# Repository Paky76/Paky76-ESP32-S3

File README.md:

# Paky76 Mini A5

Dispositivo portatile con due tasti laterali e un volto animato su **OLED SH1107G-02 da 1,5″, 128 × 128, I²C a 4 pin**. La A5 usa la **PCB principale A4** e il **frontale A1** già ordinati nella configurazione A4.1. Firmware, cablaggio, scocca e figure sono riferiti all'OLED quadrato.

## Documentazione

| Documento | Contenuto |
| --- | --- |
| [Manuale illustrato PDF](Documentazione/Paky76-Mini-A5-Manuale-Assemblaggio.pdf) | Stampa, montaggio, orientamento e collaudo |
| [Schema elettrico A3 · pagina unica](Documentazione/Paky76-Mini-A5-Schema-Elettrico.pdf) | Simboli elettrici, alimentazione, pull-up, pulsanti e OLED |
| [Tavola di cablaggio A3](Documentazione/Paky76-Mini-A5-Schema-Cablaggio-Completo.pdf) | Cablaggio tra i moduli con pin e segnali numerati |
| [Schemi di collegamento PDF](Documentazione/Paky76-Mini-A5-Schemi-Collegamento.pdf) | PCB, OLED, interruttore e batteria |
| [Datasheet PDF](Documentazione/Paky76-Mini-A5-Datasheet.pdf) | Specifiche e tavole quotate |
| [Figure e quote](Documentazione/Figure/) | Esploso, guscio, cornice, finestra, fori OLED e profilo |
| [Guida operativa](LEGGIMI.md) | Stampa, fissaggi, cablaggio, firmware e prove |

## Hardware e distinta per un dispositivo

| Qtà | Parte | Specifica |
| ---: | --- | --- |
| 1 | [Principale A4](Principale/) | 32 × 39 mm; USB-C, ingresso LiPo e pull-up I²C |
| 1 | [Frontale A1](Frontale/) | 43 × 42 mm; due tasti laterali e uscita OLED |
| 1 | U1 | Seeed XIAO ESP32-S3 113991114, C20467913 |
| 2 | J1 | JST SH 6 poli BM06B-SRSS-TB, C160392 |
| 1 | J2 frontale | JST SH 4 poli BM04B-SRSS-TB, C160390 |
| 2 | R1/R2 | 4,7 kΩ SMD 0603, C99782 |
| 2 | SW1/SW2 | Panasonic EVQP7A01P, C79167 |
| 1 | S1 | Nidec MFS201N-Z, a slitta sul fianco |
| 1 | OLED | SH1107G-02; PCB 34 × 47 mm; spessore massimo dichiarato 11,3 mm; area visibile 28,86 × 28,86 mm |
| 1 | Batteria | LiPo protetta 1S, 3,7 V nominali, 4,2 V a fine carica. Riferimento 350 mAh |
| 1 ciascuno | Cavetti | JST SH 6 vie pin per pin, JST SH 4 vie con fili lato OLED, contropresa batteria, cavo USB-C dati |
| Secondo montaggio | Fissaggi e accessori | Viti M2 da scegliere a secco, guaina isolante, ritenzione morbida cella, antenna XIAO se assente |

I [file JLCPCB](JLCPCB/) contengono Gerber, BOM e CPL per ciascuna scheda. Per PCB nudi, U1 richiede anche la saldatura dei due pad batteria sotto il modulo. Per PCBA, controllare in anteprima orientamento, componenti e montaggio.

## Cablaggio e alimentazione

**J1 principale ↔ J1 frontale**, pin per pin. 1 GND, 2 3V3, 3 SDA/GPIO5, 4 SCL/GPIO6, 5 SW1/GPIO2, 6 SW2/GPIO1. I pulsanti sono attivi bassi.

| J2 frontale | Funzione | Pin OLED secondo il disegno |
| ---: | --- | ---: |
| 1 | GND | 2 |
| 2 | 3V3 verso VCC | 1 |
| 3 | SDA | 4 |
| 4 | SCL | 3 |

Il testo commerciale e il disegno OLED riportano numerazioni di alimentazione diverse. **Seguire le serigrafie sul modulo ricevuto e collegare per segnale.** Passo JST SH 1,0 mm; lato OLED 2,54 mm. Vedere il [pinout](Cablaggio/Pinout-OLED-SH1107.md).

Il **J2 della principale** porta il positivo LiPo sul pin 1 VBAT attraverso S1 e il negativo diretto sul pin 2 GND. La prima accensione si fa via USB con batteria scollegata. Per ricaricare, portare S1 su ON. Per togliere tutta l'alimentazione, mettere S1 su OFF e scollegare USB-C.

## Scocca, montaggio e firmware

1. La scocca misura **49 × 54 × 41,6 mm**, escluse le sporgenze, e **61,5 mm** in lunghezza con occhiello. Finestra **30,4 × 30,4 mm**, centrata 3 mm verso USB-C nel CAD. Interasse nominale di fissaggio OLED **29 × 42 mm**, da confrontare con il campione.
2. In Cura importare gli [STL A5](Meccanica/) al 100%. Stampare un guscio, una cornice e due copritasti. Confrontare la dima OLED con il modulo reale prima della stampa definitiva. Il sorgente OpenSCAD è nella stessa cartella.
3. Installare S1 e la principale con USB-C opposta all'occhiello. Verificare a secco ripiano, batteria, frontale, copritasti e OLED. Montare secondo le figure, con il vetro verso la finestra e J2 del frontale verso USB-C.
4. Installare il core esp32 di Espressif e U8g2 in Arduino IDE, selezionare XIAO_ESP32S3 e usare lo [sketch A5](Firmware/Paky76MiniSH1107/Paky76MiniSH1107.ino). Il firmware cerca 0x3C e 0x3D a 100 kHz, anima il volto e risveglia il display con uno dei tasti dopo lo spegnimento per inattività. Monitor seriale a 115200 baud.
5. Verificare display, tasti e continuità prima di collegare la LiPo. Sul campione controllare passaggio dei cavi, assenza di compressione sulla cella, ricarica e temperatura con la scocca chiusa.

## Stato delle prove

I [rapporti](Verifiche/) registrano l'identità byte per byte delle PCB e dei file JLCPCB con la A4.1, il controllo delle mesh STL e la simulazione host della logica firmware. **Compilazione per la XIAO e collaudo fisico restano da eseguire.** Le quote di montaggio OLED e la corsa dei copritasti vanno verificate sul primo campione.

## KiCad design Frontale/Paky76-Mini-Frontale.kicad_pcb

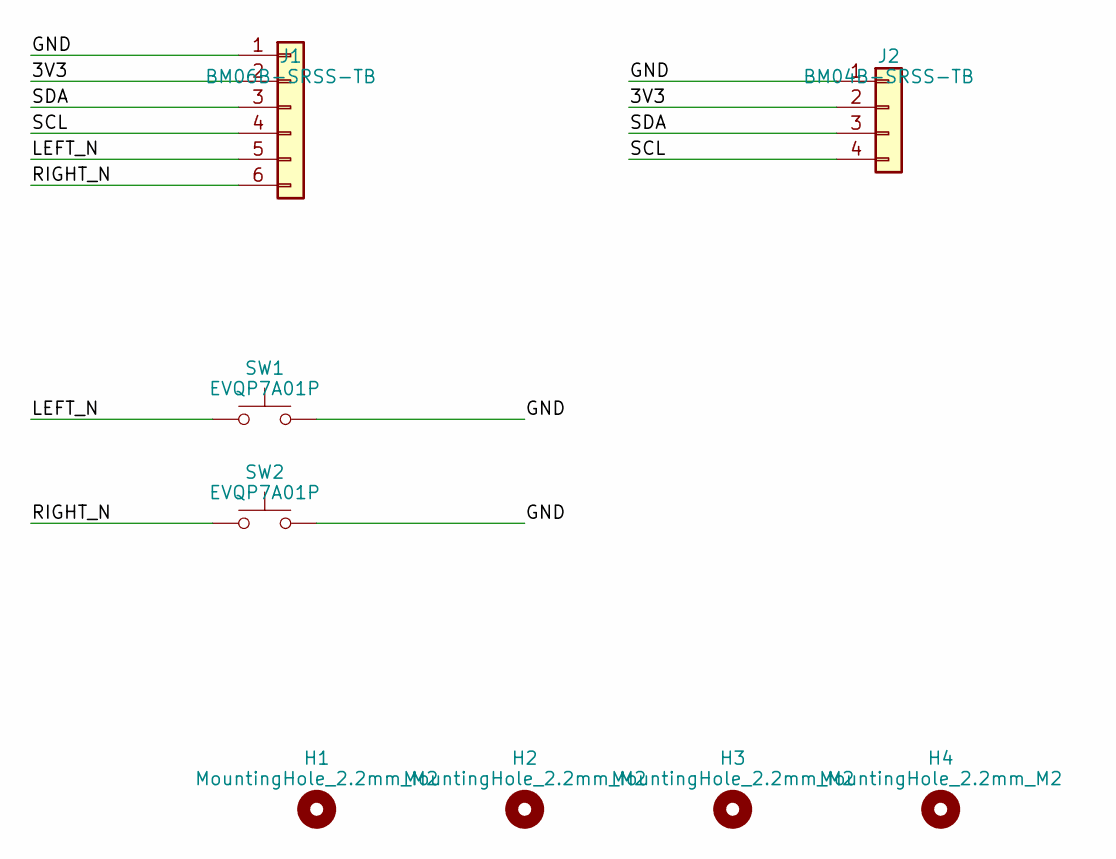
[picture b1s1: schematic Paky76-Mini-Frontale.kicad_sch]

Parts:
H1, H2, H3, H4: MountingHole_2.2mm_M2
J1: BM06B-SRSS-TB; JST_SH_BM06B-SRSS-TB_1x06-1MP_P1.00mm_Vertical
J2: BM04B-SRSS-TB; JST_SH_BM04B-SRSS-TB_1x04-1MP_P1.00mm_Vertical
SW1, SW2: EVQP7A01P; SW_SPST_EVQP7A

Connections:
/3V3: J1.2, J2.2
/GND: J1.1, J2.1, SW1.2, SW2.2
/LEFT_N: J1.5, SW1.1
/RIGHT_N: J1.6, SW2.1
/SCL: J1.4, J2.4
/SDA: J1.3, J2.3

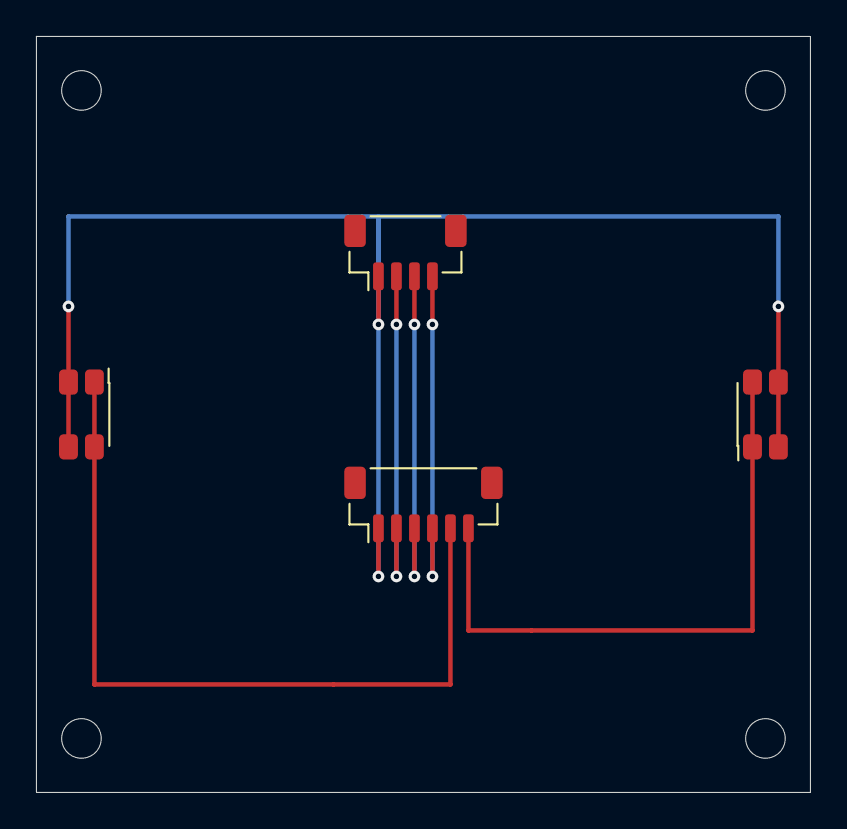
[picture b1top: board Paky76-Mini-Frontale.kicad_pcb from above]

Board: 2 copper layers, 43.0 x 42.0 mm, 8 parts (0 on the bottom side), 6 nets.

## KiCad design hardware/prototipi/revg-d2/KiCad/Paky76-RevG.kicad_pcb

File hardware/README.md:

# Hardware design workspace — Rev.A

Target: ESP32-S3-WROOM-1-based controller with external Waveshare 1.3inch LCD Module (ST7789, 240x240).

**No KiCad schematic or PCB has yet passed validation.** Do not send this directory to a board manufacturer.

## Provisional net allocation
| Net | ESP32-S3 GPIO | Peripheral |
|---|---:|---|
| LCD_MOSI | 11 | ST7789 DIN |
| LCD_SCLK | 12 | ST7789 CLK |
| LCD_CS | 10 | ST7789 CS |
| LCD_DC | 9 | ST7789 DC |
| LCD_RST | 8 | ST7789 RST |
| LCD_BL | 7 | ST7789 BL (driver TBD) |
| USB_DN | 19 | USB D- |
| USB_DP | 20 | USB D+ |

Verify the exact Waveshare module pin sequence and mating connector orientation before routing. GPIO7 must not be connected directly to a high-current backlight load without checking the module's BL interface.

## Design blocks to capture in KiCad
1. U1 ESP32-S3-WROOM-1, validated footprint and antenna keepout.
2. J1 USB-C receptacle, USB2.0 D+/D-, CC resistors and ESD.
3. U2 3.3 V regulator sized for ESP32-S3 radio bursts and display.
4. Boot/reset circuitry, EN pull-up and programming access.
5. LCD 8-pin PH2.0 mating connector, pin-1 orientation checked.
6. Power decoupling, test points, mounting and mechanical outline.

Manufacturing deliverables are gated on actual KiCad ERC/DRC and independent review.

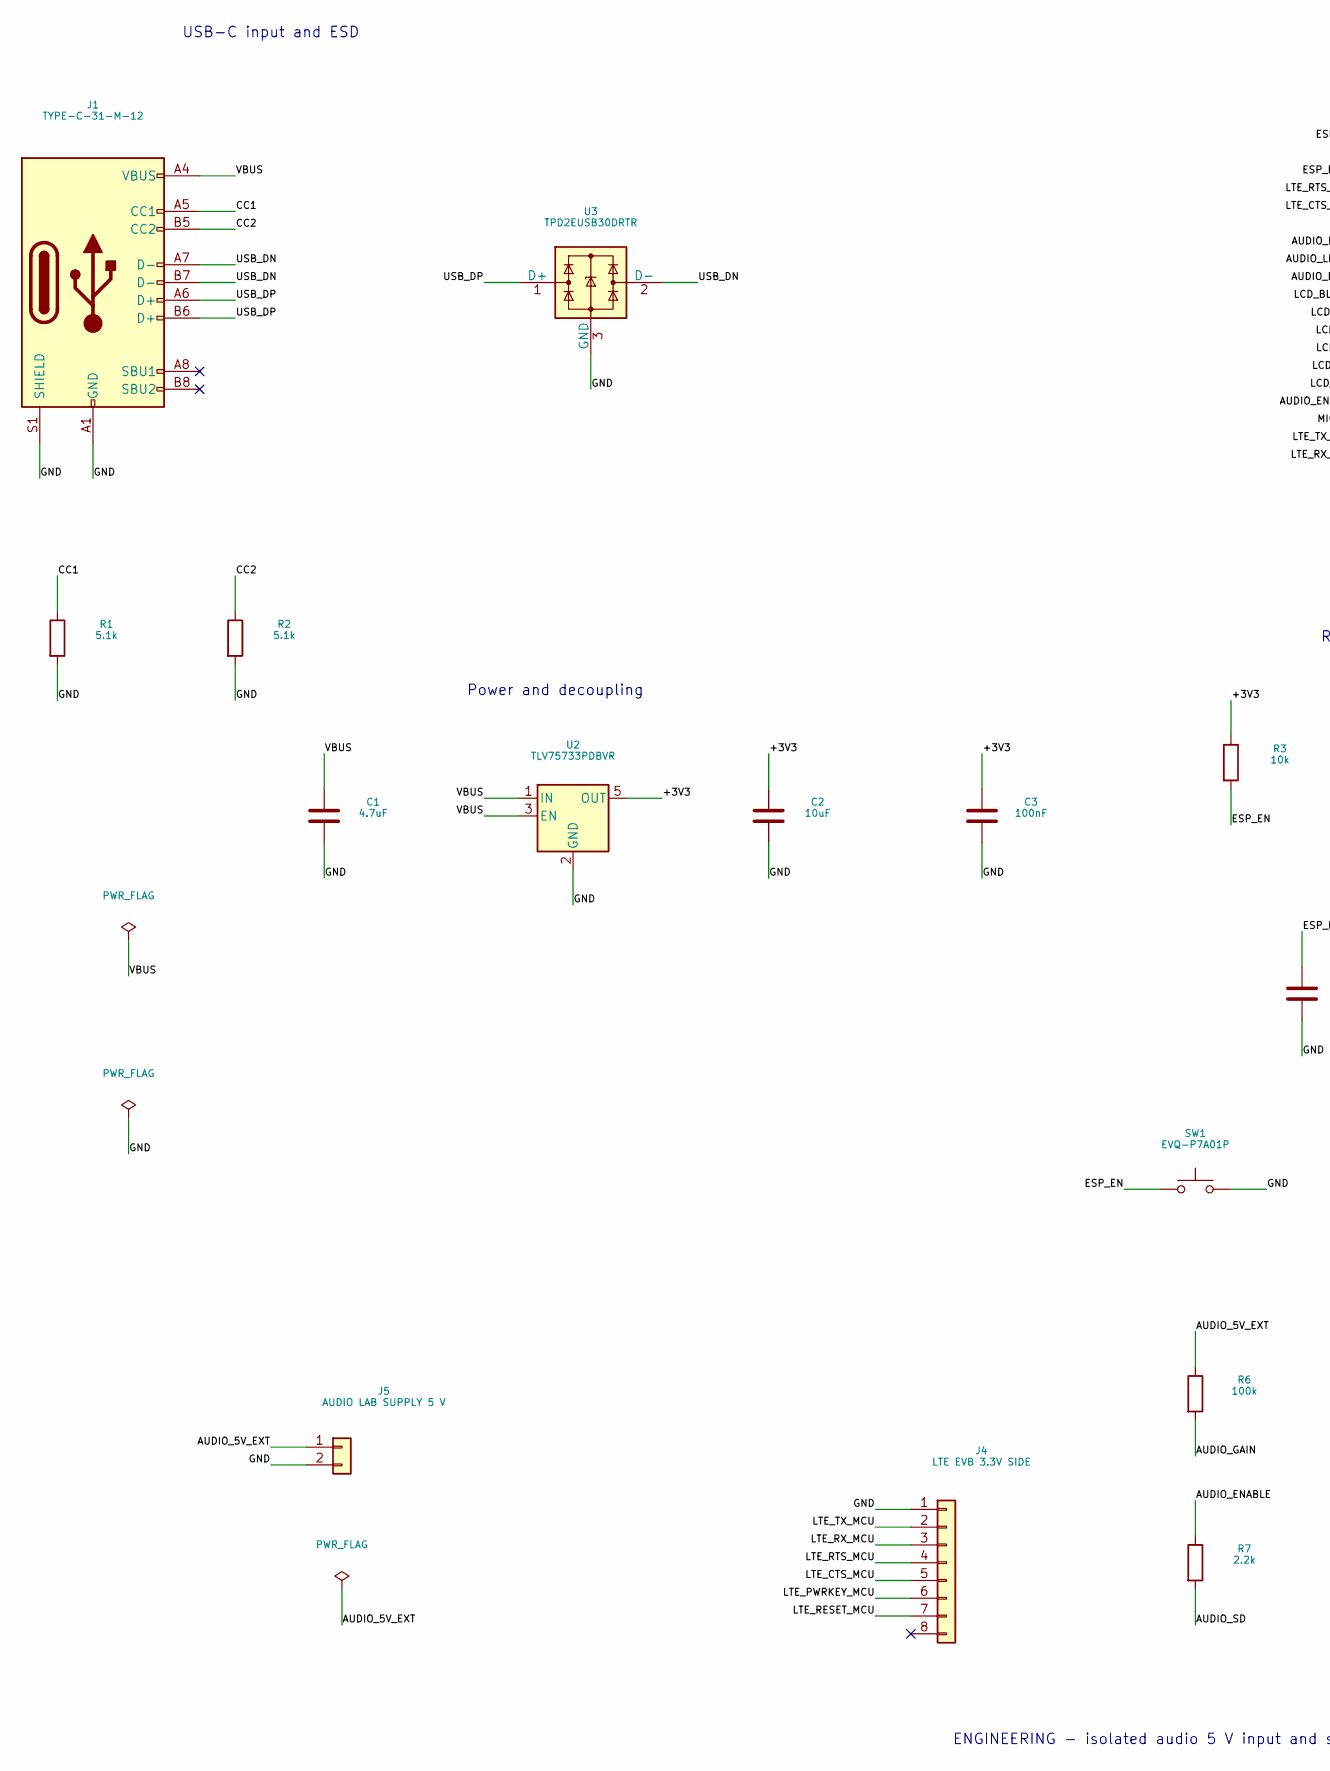
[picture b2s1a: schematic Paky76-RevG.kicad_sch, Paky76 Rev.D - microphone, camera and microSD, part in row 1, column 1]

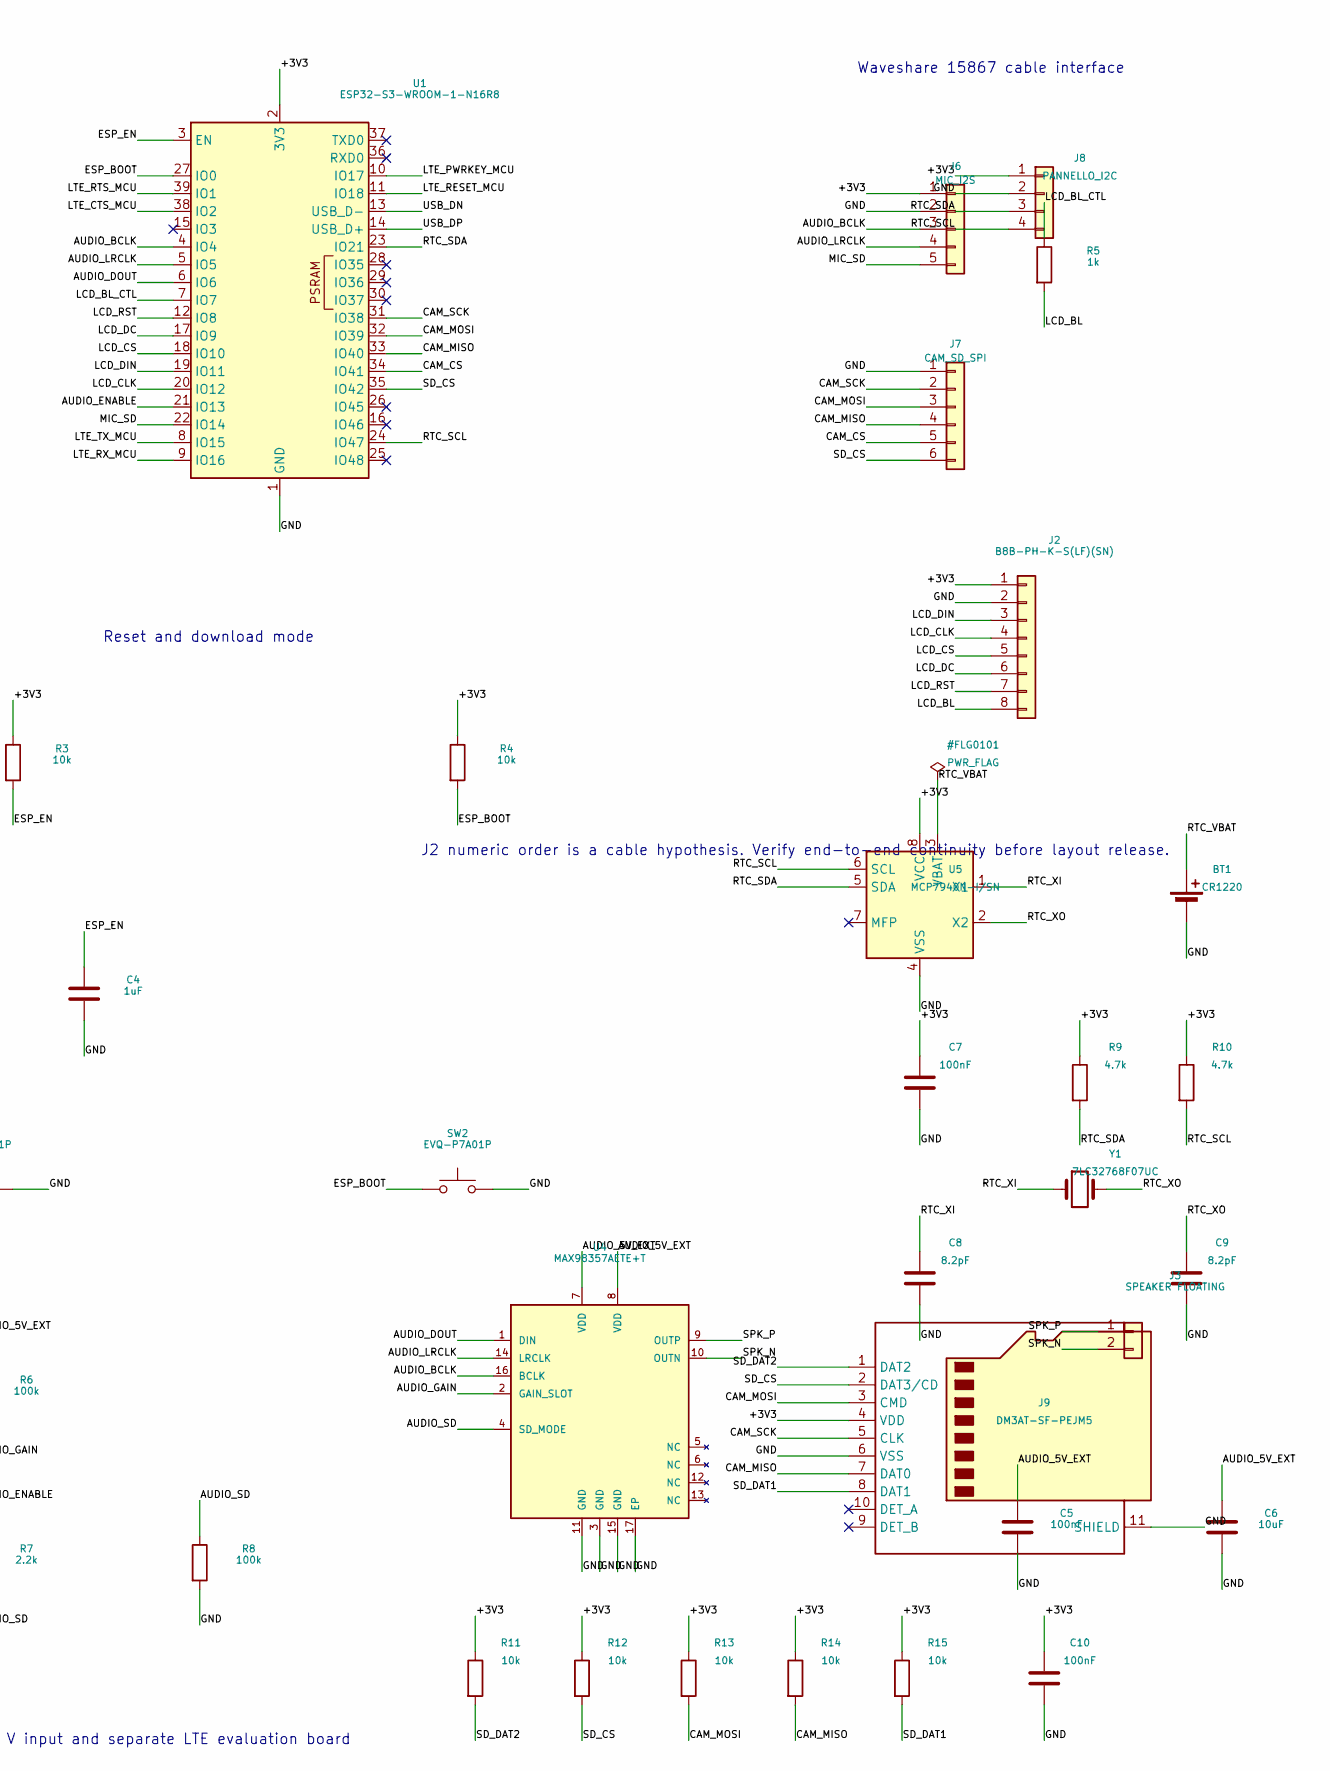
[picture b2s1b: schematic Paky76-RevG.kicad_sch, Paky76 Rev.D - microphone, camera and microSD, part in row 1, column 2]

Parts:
BT1: CR1220; BatteryHolder_Keystone_500
C1: 4.7uF; C_0805_2012Metric
C2, C6: 10uF; C_0805_2012Metric
C3, C5, C7, C10: 100nF; C_0603_1608Metric
C4: 1uF; C_0603_1608Metric
C8, C9: 8.2pF; C_0603_1608Metric
J1: TYPE-C-31-M-12; USB_C_HRO_TYPE-C-31-M-12_Edge
J2: B8B-PH-K-S(LF)(SN); JST_PH_B8B-PH-K_1x08_P2.00mm_Vertical
J3: SPEAKER FLOATING; JST_PH_B2B-PH-K_1x02_P2.00mm_Vertical
J4: LTE EVB 3.3V SIDE; PinHeader_1x08_P2.54mm_Vertical
J5: AUDIO LAB SUPPLY 5 V; JST_PH_B2B-PH-K_1x02_P2.00mm_Vertical
J6: MIC_I2S; JST_PH_B5B-PH-K_1x05_P2.00mm_Vertical
J7: CAM_SD_SPI; JST_PH_B6B-PH-K_1x06_P2.00mm_Vertical
J8: PANNELLO_I2C; JST_SH_BM04B-SRSS-TB_1x04-1MP_P1.00mm_Vertical
J9: DM3AT-SF-PEJM5; microSD_HC_Hirose_DM3AT-SF-PEJM5
R1, R2: 5.1k; R_0603_1608Metric
R3, R4, R11, R12, R13, R14, R15: 10k; R_0603_1608Metric
R5: 1k; R_0603_1608Metric
R6, R8: 100k; R_0603_1608Metric
R7: 2.2k; R_0603_1608Metric
R9, R10: 4.7k; R_0603_1608Metric
SW1, SW2: EVQ-P7A01P; SW_SPST_EVQP7A
U1: ESP32-S3-WROOM-1-N16R8; ESP32-S3-WROOM-1_4L_Overhang
U2: TLV75733PDBVR; SOT-23-5
U3: TPD2EUSB30DRTR; Texas_DRT-3
U4: MAX98357AETE+T; MAX98357A_T1633_90-0031
U5: MCP7940N-I/SN; SOIC-8_3.9x4.9mm_P1.27mm
Y1: 7LC32768F07UC; Crystal_SMD_3215-2Pin_3.2x1.5mm

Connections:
/+3V3: C2.1, C3.1, C7.1, C10.1, J2.1, J6.1, J8.1, J9.4 (VDD), R3.1, R4.1, R9.1, R10.1, R11.1, R12.1, R13.1, R14.1, R15.1, U1.2 (3V3), U2.5 (OUT), U5.8 (VCC)
/AUDIO_5V_EXT: C5.1, C6.1, J5.1, R6.1, U4.7 (VDD), U4.8 (VDD)
/AUDIO_BCLK: J6.3, U1.4 (IO4), U4.16 (BCLK)
/AUDIO_DOUT: U1.6 (IO6), U4.1 (DIN)
/AUDIO_ENABLE: R7.1, U1.21 (IO13)
/AUDIO_GAIN: R6.2, U4.2 (GAIN_SLOT)
/AUDIO_LRCLK: J6.4, U1.5 (IO5), U4.14 (LRCLK)
/AUDIO_SD: R7.2, R8.1, U4.4 (SD_MODE)
/CAM_CS: J7.5, U1.34 (IO41)
/CAM_MISO: J7.4, J9.7 (DAT0), R14.2, U1.33 (IO40)
/CAM_MOSI: J7.3, J9.3 (CMD), R13.2, U1.32 (IO39)
/CAM_SCK: J7.2, J9.5 (CLK), U1.31 (IO38)
/CC1: J1.A5 (CC1), R1.1
/CC2: J1.B5 (CC2), R2.1
/ESP_BOOT: R4.2, SW2.1, U1.27 (IO0)
/ESP_EN: C4.1, R3.2, SW1.1, U1.3 (EN)
/GND: BT1.2 (-), C1.2, C2.2, C3.2, C4.2, C5.2, C6.2, C7.2, C8.2, C9.2, C10.2, J1.A1 (GND), J1.A12 (GND), J1.B1 (GND), J1.B12 (GND), J1.S1 (SHIELD), J2.2, J4.1, J5.2, J6.2, J7.1, J8.2, J9.6 (VSS), J9.11 (SHIELD), R1.2, R2.2, R8.2, SW1.2, SW2.2, U1.1 (GND), U1.40 (GND), U1.41 (GND), U2.2 (GND), U3.3 (GND), U4.3 (GND), U4.11 (GND), U4.15 (GND), U4.17 (EP), U5.4 (VSS)
/LCD_BL: J2.8, R5.2
/LCD_BL_CTL: R5.1, U1.7 (IO7)
/LCD_CLK: J2.4, U1.20 (IO12)
/LCD_CS: J2.5, U1.18 (IO10)
/LCD_DC: J2.6, U1.17 (IO9)
/LCD_DIN: J2.3, U1.19 (IO11)
/LCD_RST: J2.7, U1.12 (IO8)
/LTE_CTS_MCU: J4.5, U1.38 (IO2)
/LTE_PWRKEY_MCU: J4.6, U1.10 (IO17)
/LTE_RESET_MCU: J4.7, U1.11 (IO18)
/LTE_RTS_MCU: J4.4, U1.39 (IO1)
/LTE_RX_MCU: J4.3, U1.9 (IO16)
/LTE_TX_MCU: J4.2, U1.8 (IO15)
/MIC_SD: J6.5, U1.22 (IO14)
/RTC_SCL: J8.4, R10.2, U1.24 (IO47), U5.6 (SCL)
/RTC_SDA: J8.3, R9.2, U1.23 (IO21), U5.5 (SDA)
/RTC_VBAT: BT1.1 (+), U5.3 (VBAT)
/RTC_XI: C8.1, U5.1 (X1), Y1.1
/RTC_XO: C9.1, U5.2 (X2), Y1.2
/SD_CS: J7.6, J9.2 (DAT3/CD), R12.2, U1.35 (IO42)
/SD_DAT1: J9.8 (DAT1), R15.2
/SD_DAT2: J9.1 (DAT2), R11.2
/SPK_N: J3.2, U4.10 (OUTN)
/SPK_P: J3.1, U4.9 (OUTP)
/USB_DN: J1.A7 (D-), J1.B7 (D-), U1.13 (USB_D-), U3.2 (D-)
/USB_DP: J1.A6 (D+), J1.B6 (D+), U1.14 (USB_D+), U3.1 (D+)
/VBUS: C1.1, J1.A4 (VBUS), J1.A9 (VBUS), J1.B4 (VBUS), J1.B9 (VBUS), U2.1 (IN), U2.3 (EN)

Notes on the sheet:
USB-C input and ESD
Power and decoupling
Reset and download mode
Waveshare 15867 cable interface
J2 numeric order is a cable hypothesis. Verify end-to-end continuity before layout release.
ENGINEERING - isolated audio 5 V input and separate LTE evaluation board

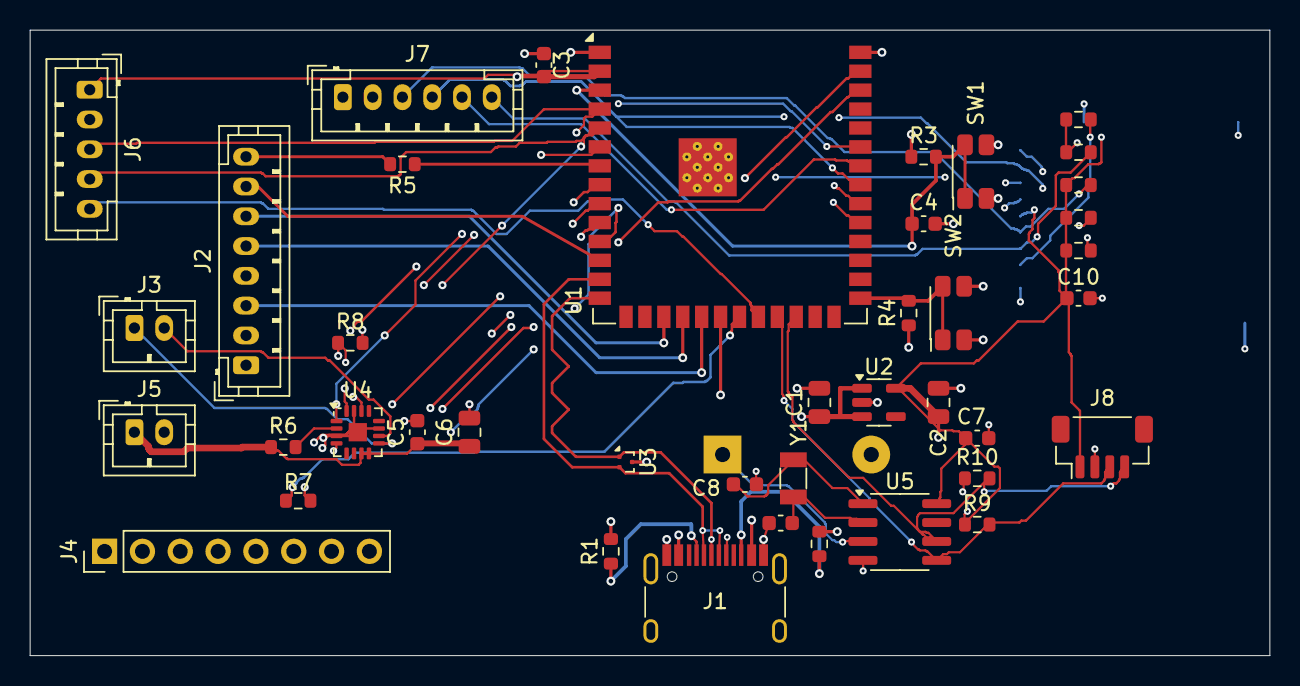
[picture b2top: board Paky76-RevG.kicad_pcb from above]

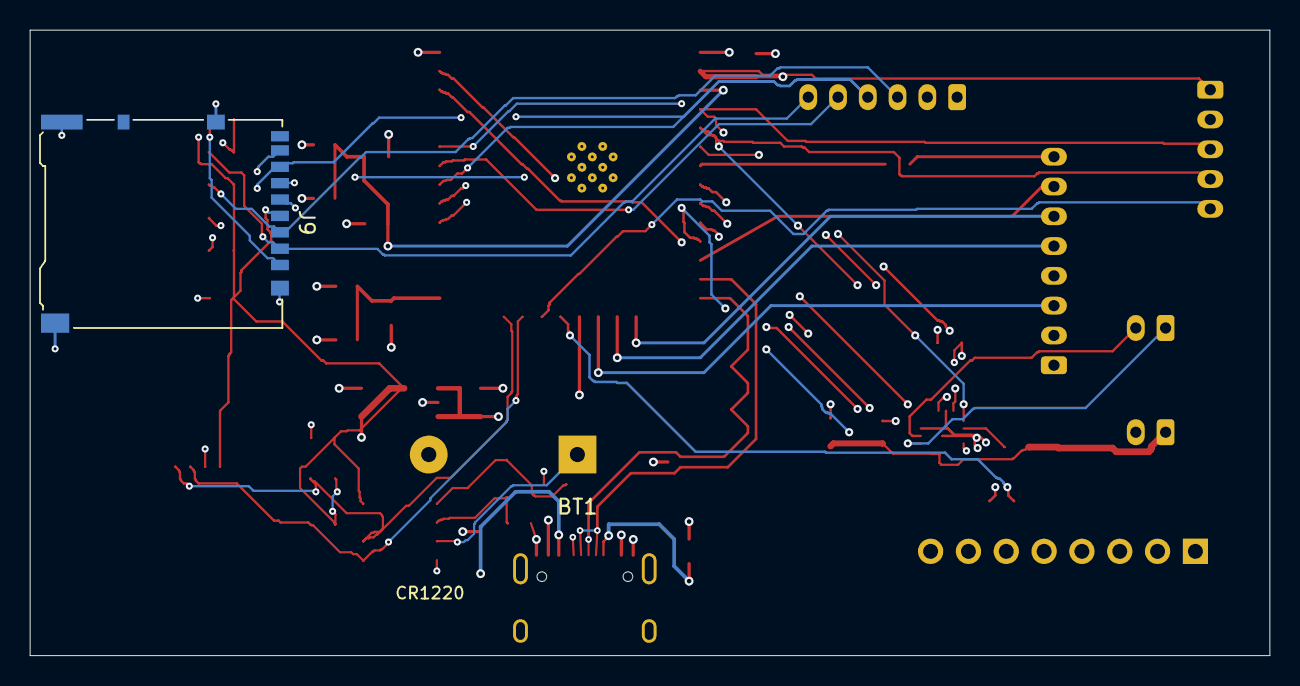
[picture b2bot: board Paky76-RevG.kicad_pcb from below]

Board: 4 copper layers, 83.2 x 42.0 mm, 43 parts (2 on the bottom side), 44 nets.

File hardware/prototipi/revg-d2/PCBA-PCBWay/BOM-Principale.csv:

Comment,Designator,Footprint,Manufacturer Part Number,LCSC Part #
4.7uF,C1,C_0805_2012Metric,GRM21BR71C475KA73L,C86040
10uF,"C2,C6",C_0805_2012Metric,GRM21BR71A106KE51L,C86038
100nF,"C3,C5,C7,C10",C_0603_1608Metric,GRM188R71C104KA01D,C45000
1uF,C4,C_0603_1608Metric,GRT188R71C105KE13D,C6627646
TYPE-C-31-M-12,J1,USB_C_HRO_TYPE-C-31-M-12_Edge,TYPE-C-31-M-12,C165948
B8B-PH-K-S(LF)(SN),J2,JST_PH_B8B-PH-K_1x08_P2.00mm_Vertical,B8B-PH-K-S(LF)(SN),C157974
B2B-PH-K-S(LF)(SN),"J3,J5",JST_PH_B2B-PH-K_1x02_P2.00mm_Vertical,B2B-PH-K-S(LF)(SN),C131337
LTE EVB 3.3V SIDE,J4,PinHeader_1x08_P2.54mm_Vertical,TSW-108-07-G-S,C3335496
5.1k,"R1,R2",R_0603_1608Metric,RC0603FR-075K1L,C105580
10k,"R3,R4,R11,R12,R13,R14,R15",R_0603_1608Metric,RC0603FR-0710KL,C98220
1k,R5,R_0603_1608Metric,RC0603FR-071KL,C22548
100k,"R6,R8",R_0603_1608Metric,RC0603FR-07100KL,C14675
2.2k,R7,R_0603_1608Metric,RC0603FR-072K2L,C114662
EVQ-P7A01P,"SW1,SW2",SW_SPST_EVQP7A,EVQP7A01P,C79167
ESP32-S3-WROOM-1-N16R8,U1,ESP32-S3-WROOM-1_4L_Overhang,ESP32-S3-WROOM-1-N16R8,C2913202
TLV75733PDBVR,U2,SOT-23-5,TLV75733PDBVR,C485517
TPD2EUSB30DRTR,U3,Texas_DRT-3,TPD2EUSB30DRTR,C97502
MAX98357AETE+T,U4,MAX98357A_T1633_90-0031,MAX98357AETE+T,C910544
B5B-PH-K-S(LF)(SN),J6,JST_PH_B5B-PH-K_1x05_P2.00mm_Vertical,B5B-PH-K-S(LF)(SN),C157993
B6B-PH-K-S(LF)(SN),J7,JST_PH_B6B-PH-K_1x06_P2.00mm_Vertical,B6B-PH-K-S(LF)(SN),C131342
4.7k,"R9,R10",R_0603_1608Metric,RC0603FR-074K7L,C99782
MCP7940N-I/SN,U5,SOIC-8_3.9x4.9mm_P1.27mm,MCP7940N-I/SN,C51106
CR1220 holder,BT1,BatteryHolder_Keystone_500,500,C238121
32.768kHz 7pF,Y1,Crystal_SMD_3215-2Pin_3.2x1.5mm,7LC32768F07UC,C252399
8.2pF C0G,"C8,C9",C_0603_1608Metric,TCC0603COG8R2C500CT,C376804
BM04B-SRSS-TB,J8,JST_SH_BM04B-SRSS-TB_1x04-1MP_P1.00mm_Vertical,BM04B-SRSS-TB(LF)(SN),C160390
Hirose microSD,J9,microSD_HC_Hirose_DM3AT-SF-PEJM5,DM3AT-SF-PEJM5,C114218

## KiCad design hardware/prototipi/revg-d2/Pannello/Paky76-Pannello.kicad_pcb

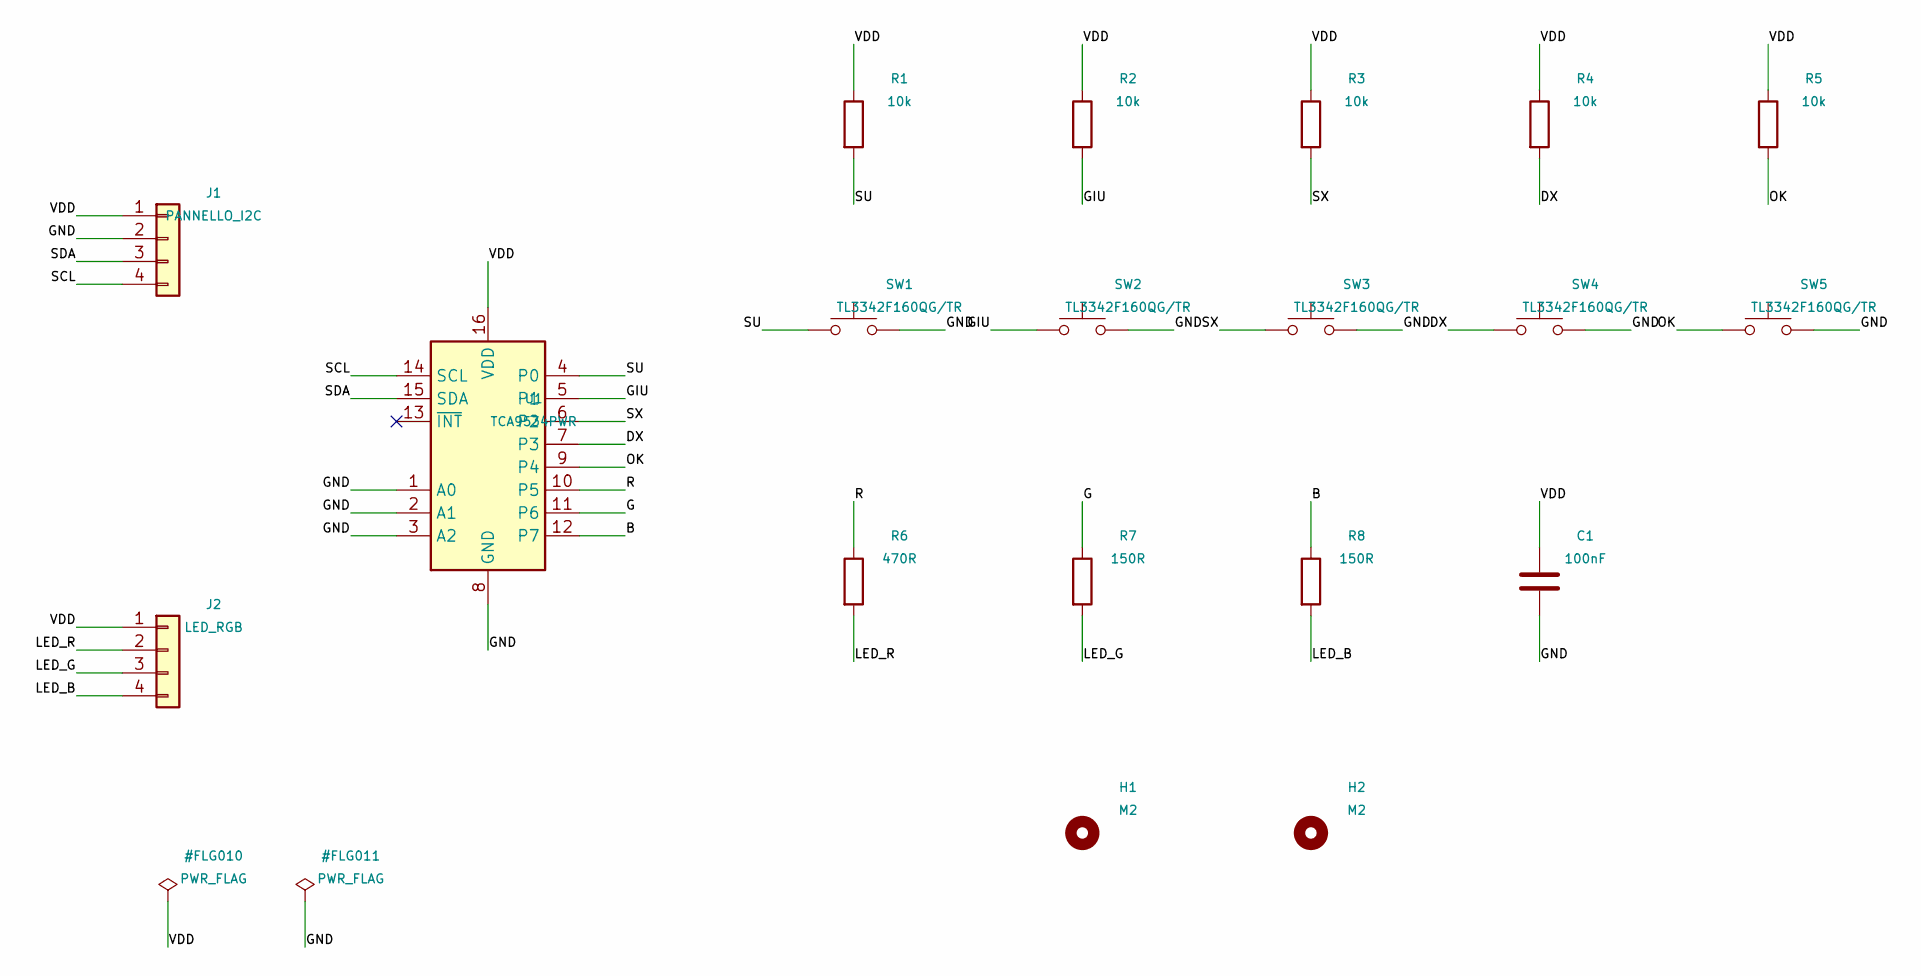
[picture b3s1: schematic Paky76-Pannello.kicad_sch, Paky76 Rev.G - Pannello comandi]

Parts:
C1: 100nF; C_0603_1608Metric
H1, H2: M2; MountingHole_2.2mm_M2
J1: PANNELLO_I2C; JST_SH_BM04B-SRSS-TB_1x04-1MP_P1.00mm_Vertical
J2: LED_RGB; JST_SH_BM04B-SRSS-TB_1x04-1MP_P1.00mm_Vertical
R1, R2, R3, R4, R5: 10k; R_0603_1608Metric
R6: 470R; R_0603_1608Metric
R7, R8: 150R; R_0603_1608Metric
SW1, SW2, SW3, SW4, SW5: TL3342F160QG/TR; SW_SPST_TL3342
U1: TCA9534PWR; TSSOP-16_4.4x5mm_P0.65mm

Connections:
/B: R8.1, U1.12 (P7)
/DX: R4.2, SW4.1, U1.7 (P3)
/G: R7.1, U1.11 (P6)
/GIU: R2.2, SW2.1, U1.5 (P1)
/GND: C1.2, J1.2, SW1.2, SW2.2, SW3.2, SW4.2, SW5.2, U1.1 (A0), U1.2 (A1), U1.3 (A2), U1.8 (GND)
/LED_B: J2.4, R8.2
/LED_G: J2.3, R7.2
/LED_R: J2.2, R6.2
/OK: R5.2, SW5.1, U1.9 (P4)
/R: R6.1, U1.10 (P5)
/SCL: J1.4, U1.14 (SCL)
/SDA: J1.3, U1.15 (SDA)
/SU: R1.2, SW1.1, U1.4 (P0)
/SX: R3.2, SW3.1, U1.6 (P2)
/VDD: C1.1, J1.1, J2.1, R1.1, R2.1, R3.1, R4.1, R5.1, U1.16 (VDD)

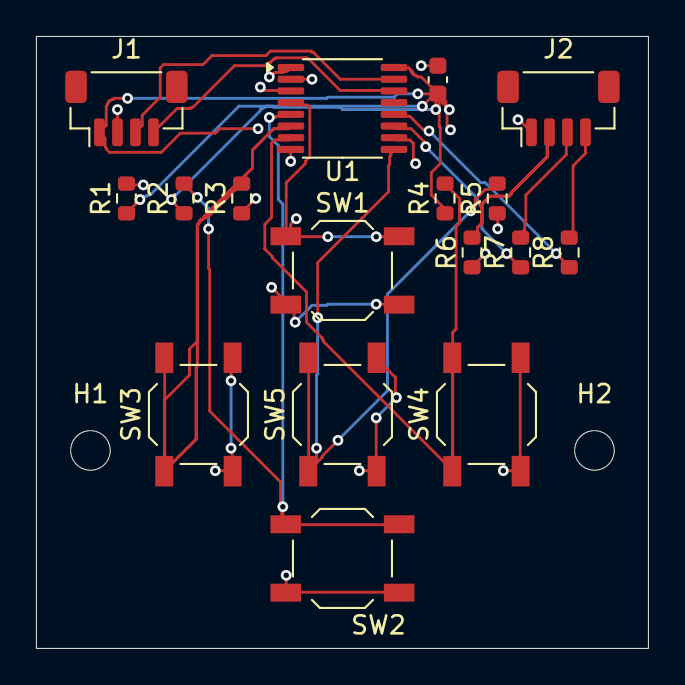
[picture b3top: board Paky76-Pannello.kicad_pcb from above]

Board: 4 copper layers, 34.0 x 34.0 mm, 19 parts (0 on the bottom side), 15 nets.

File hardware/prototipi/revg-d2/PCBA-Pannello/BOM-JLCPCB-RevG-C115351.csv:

Comment,Designator,Footprint,Manufacturer Part Number,LCSC Part #
100nF,C1,C_0603_1608Metric,GRM188R71C104KA01D,C45000
BM04B-SRSS-TB,"J1,J2",JST_SH_BM04B-SRSS-TB_1x04-1MP_P1.00mm_Vertical,BM04B-SRSS-TB(LF)(SN),C160390
TCA9534,U1,TSSOP-16_4.4x5mm_P0.65mm,TCA9534PWR,C783615
Five tactile switches,"SW1,SW2,SW3,SW4,SW5",SW_SPST_TL3342,SKQGABE010,C115351
10k,"R1,R2,R3,R4,R5",R_0603_1608Metric,RC0603FR-0710KL,C98220
470R,R6,R_0603_1608Metric,RC0603FR-07470RL,C114669
150R,"R7,R8",R_0603_1608Metric,RC0603FR-07150RL,C114608

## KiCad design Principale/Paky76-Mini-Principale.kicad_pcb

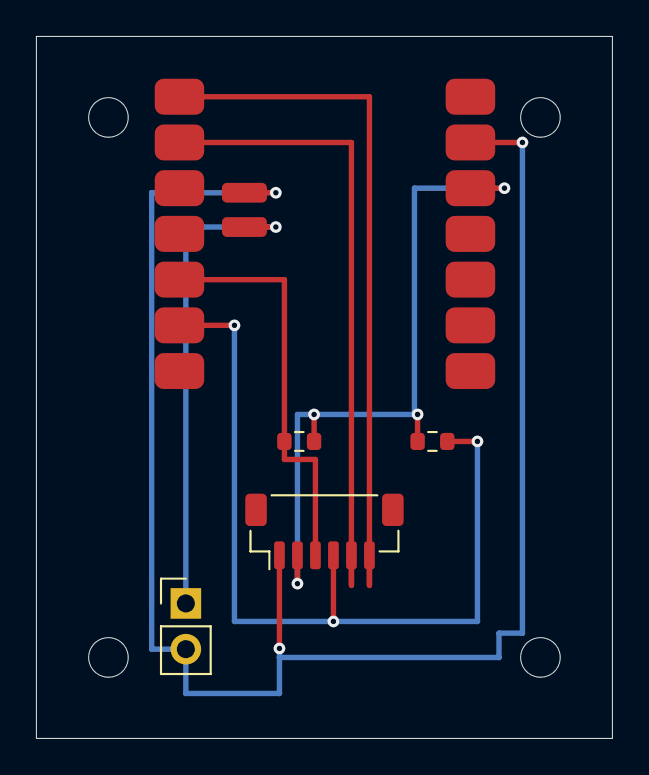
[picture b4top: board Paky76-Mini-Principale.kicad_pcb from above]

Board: 2 copper layers, 32.0 x 39.0 mm, 9 parts (0 on the bottom side), 7 nets.

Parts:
H1, H2, H3, H4: MountingHole_2.2mm_M2
J1: BM06B-SRSS-TB; JST_SH_BM06B-SRSS-TB_1x06-1MP_P1.00mm_Vertical
J2: BAT-SW; PinHeader_1x02_P2.54mm_Vertical
R1, R2: 4.7k; R_0603_1608Metric
U1: 113991114; XIAO-ESP32-S3-PCBA

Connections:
/3V3: J1.2, R1.2, R2.1, U1.12
/GND: J1.1, J2.2, U1.13, U1.16
/LEFT_N: J1.5, U1.2
/RIGHT_N: J1.6, U1.1
/SCL: J1.4, R2.2, U1.6
/SDA: J1.3, R1.1, U1.5
/VBAT: J2.1, U1.15

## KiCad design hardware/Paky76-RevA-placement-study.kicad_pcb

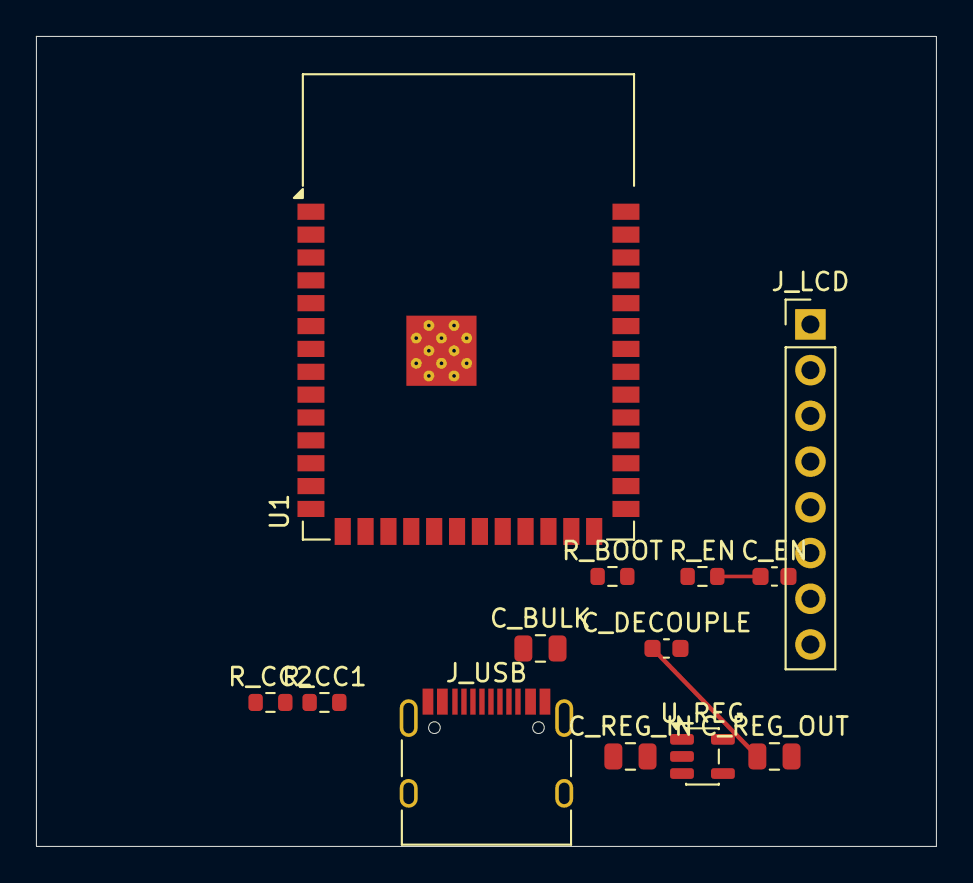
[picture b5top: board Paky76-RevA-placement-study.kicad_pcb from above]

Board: 2 copper layers, 50.0 x 45.0 mm, 13 parts (0 on the bottom side), 15 nets.

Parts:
C_BULK: 10uF_PLACEHOLDER; C_0805_2012Metric
C_DECOUPLE: 100nF_PLACEHOLDER; C_0603_1608Metric
C_EN: 1uF_CANDIDATE; C_0603_1608Metric
C_REG_IN: 10uF_CANDIDATE; C_0805_2012Metric
C_REG_OUT: 10uF_CANDIDATE; C_0805_2012Metric
J_LCD: DISPLAY_INTERFACE_STUDY_ONLY; PinHeader_1x08_P2.54mm_Vertical
J_USB: USB-C_FOOTPRINT_STUDY; USB_C_Receptacle_HRO_TYPE-C-31-M-12
R_BOOT: 10k_CANDIDATE; R_0603_1608Metric
R_CC1, R_CC2: 5.1k; R_0603_1608Metric
R_EN: 10k_CANDIDATE; R_0603_1608Metric
U1: ESP32-S3-WROOM-1-N8; ESP32-S3-WROOM-1
U_REG: AP2112K-3.3TRG1_CANDIDATE; SOT-23-5

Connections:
+3V3: C_DECOUPLE.1, C_REG_OUT.1, J_LCD.2, R_BOOT.1, R_EN.1, U1.2, U_REG.5
ESP_EN: C_EN.1, R_EN.2, U1.3
ESP_GPIO0_BOOT: R_BOOT.2, U1.27
GND: C_BULK.2, C_DECOUPLE.2, C_EN.2, C_REG_IN.2, C_REG_OUT.2, J_LCD.1, J_USB.A1, J_USB.A12, J_USB.B1, J_USB.B12, R_CC1.2, R_CC2.2, U1.1, U1.40, U1.41, U_REG.2
LCD_BL: J_LCD.8, U1.7
LCD_CS: J_LCD.7, U1.18
LCD_DC: J_LCD.6, U1.17
LCD_MOSI: J_LCD.4, U1.19
LCD_RST: J_LCD.5, U1.12
LCD_SCLK: J_LCD.3, U1.20
USB_CC1: J_USB.A5, R_CC1.1
USB_CC2: J_USB.B5, R_CC2.1
USB_DN: J_USB.A7, J_USB.B7, U1.13
USB_DP: J_USB.A6, J_USB.B6, U1.14
USB_VBUS_5V: C_BULK.1, C_REG_IN.1, J_USB.A4, J_USB.A9, J_USB.B4, J_USB.B9, U_REG.1, U_REG.3

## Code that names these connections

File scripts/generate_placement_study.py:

#!/usr/bin/env python3
"""Generate an editable but electrically INCOMPLETE KiCad PCB study. NOT FOR FABRICATION."""
import os
import pcbnew as pcb

OUT = os.environ.get("PAKY76_BOARD_OUT", "hardware/Paky76-RevA-placement-study.kicad_pcb")
board = pcb.BOARD()
def mm(x): return pcb.FromMM(x)
def vec(x,y): return pcb.VECTOR2I(mm(x),mm(y))
def add_footprint(lib, name, ref, value, x, y, rotation=0):
    fp=pcb.FootprintLoad("/usr/share/kicad/footprints/"+lib+".pretty", name)
    if fp is None: raise RuntimeError(f"Missing KiCad footprint: {lib}:{name}")
    fp.SetReference(ref)
    fp.SetValue(value)
    fp.SetPosition(vec(x,y))
    fp.SetOrientationDegrees(rotation)
    board.Add(fp)
    return fp
def edge(x1,y1,x2,y2):
    s=pcb.PCB_SHAPE(board)
    s.SetShape(pcb.SHAPE_T_SEGMENT)
    s.SetStart(vec(x1,y1));s.SetEnd(vec(x2,y2))
    s.SetLayer(pcb.Edge_Cuts);s.SetWidth(mm(.05))
    board.Add(s)
# Placement study: dimensions subject to antenna, USB, and enclosure review.
for a,b,c,d in [(100,100,150,100),(150,100,150,145),(150,145,100,145),(100,145,100,100)]: edge(a,b,c,d)
esp=add_footprint("RF_Module","ESP32-S3-WROOM-1","U1","ESP32-S3-WROOM-1-N8",124,115)
lcd=add_footprint("Connector_PinHeader_2.54mm","PinHeader_1x08_P2.54mm_Vertical","J_LCD","DISPLAY_INTERFACE_STUDY_ONLY",143,116)
usb=add_footprint("Connector_USB","USB_C_Receptacle_HRO_TYPE-C-31-M-12","J_USB","USB-C_FOOTPRINT_STUDY",125,141)
cc1=add_footprint("Resistor_SMD","R_0603_1608Metric","R_CC1","5.1k",116,137)
cc2=add_footprint("Resistor_SMD","R_0603_1608Metric","R_CC2","5.1k",113,137)
bulk=add_footprint("Capacitor_SMD","C_0805_2012Metric","C_BULK","10uF_PLACEHOLDER",128,134)
dec=add_footprint("Capacitor_SMD","C_0603_1608Metric","C_DECOUPLE","100nF_PLACEHOLDER",135,134)
reg=add_footprint("Package_TO_SOT_SMD","SOT-23-5","U_REG","AP2112K-3.3TRG1_CANDIDATE",137,140)
reg_in=add_footprint("Capacitor_SMD","C_0805_2012Metric","C_REG_IN","10uF_CANDIDATE",133,140)
reg_out=add_footprint("Capacitor_SMD","C_0805_2012Metric","C_REG_OUT","10uF_CANDIDATE",141,140)
en_pullup=add_footprint("Resistor_SMD","R_0603_1608Metric","R_EN","10k_CANDIDATE",137,130)
en_cap=add_footprint("Capacitor_SMD","C_0603_1608Metric","C_EN","1uF_CANDIDATE",141,130)
boot_pullup=add_footprint("Resistor_SMD","R_0603_1608Metric","R_BOOT","10k_CANDIDATE",132,130)
# Preliminary USB-C sink pad net assignments on the real KiCad pads.
# Only these connector pads are mapped. This is NOT a schematic or routed design.
def net(name):
    n=pcb.NETINFO_ITEM(board,name)
    board.Add(n)
    return n
def assign(fp,number,network):
    pads=[p for p in fp.Pads() if p.GetNumber()==number]
    if not pads:
        raise RuntimeError("Footprint %s missing required pad %s"%(fp.GetReference(),number))
    for p in pads: p.SetNet(network)
gnd=net("GND")
vbus=net("USB_VBUS_5V")
cc1net=net("USB_CC1")
cc2net=net("USB_CC2")
v33=net("+3V3")
en=net("ESP_EN")
boot=net("ESP_GPIO0_BOOT")
for number in ("A1","A12","B1","B12"):
    assign(usb,number,gnd)
for number in ("A4","A9","B4","B9"):
    assign(usb,number,vbus)
assign(usb,"A5",cc1net)
assign(usb,"B5",cc2net)
assign(cc1,"1",cc1net)
assign(cc1,"2",gnd)
assign(cc2,"1",cc2net)
assign(cc2,"2",gnd)
# Candidate AP2112K SOT-23-5: 1 VIN, 2 GND, 3 EN, 4 NC, 5 VOUT.
for pin,network in (("1",vbus),("2",gnd),("3",vbus),("5",v33)):
    assign(reg,pin,network)
for capacitor,rail in ((reg_in,vbus),(reg_out,v33),(bulk,vbus),(dec,v33)):
    assign(capacitor,"1",rail)
    assign(capacitor,"2",gnd)
assign(esp,"3",en)
assign(esp,"27",boot)
assign(en_pullup,"1",v33)
assign(en_pullup,"2",en)
assign(en_cap,"1",en)
assign(en_cap,"2",gnd)
assign(boot_pullup,"1",v33)
assign(boot_pullup,"2",boot)
# ESP32-S3-WROOM-1 physical castellated pad mapping (candidate, verify with
# exact module revision/datasheet before manufacturing).
# ESP pad 2: 3V3, pad 1: GND, pad 3: EN; USB native D-/D+ pads 13/14.
usb_dn=net("USB_DN")
usb_dp=net("USB_DP")
for pin in ("A7","B7"):
    assign(usb,pin,usb_dn)
for pin in ("A6","B6"):
    assign(usb,pin,usb_dp)
for pin,network in (("1",gnd),("2",v33),("13",usb_dn),("14",usb_dp)):
    assign(esp,pin,network)
# EN and remaining module GND pins deliberately not wired: schematic pending.
# Native ESP32-S3 module pad numbers for the proposed ST7789 SPI bus.
# Provisional 8-pin ST7789 breakout header: GND,VCC,SCL,SDA,RES,DC,CS,BLK.
# WARNING: modules differ; this pin order is an ASSUMPTION, not a verified part.
lcd_signals={"LCD_MOSI":"19","LCD_SCLK":"20","LCD_CS":"18",
             "LCD_DC":"17","LCD_RST":"12","LCD_BL":"7"}
lcd_nets={}
for signal,pin in lcd_signals.items():
    lcd_nets[signal]=net(signal)
    assign(esp,pin,lcd_nets[signal])
for pin,network in (("1",gnd),("2",v33),("3",lcd_nets["LCD_SCLK"]),
                    ("4",lcd_nets["LCD_MOSI"]),("5",lcd_nets["LCD_RST"]),
                    ("6",lcd_nets["LCD_DC"]),("7",lcd_nets["LCD_CS"]),
                    ("8",lcd_nets["LCD_BL"])):
    assign(lcd,pin,network)
# Pad 41 is a multi-aperture exposed GND pad (12 small plated holes).
# assign() deliberately applies the net to ALL pads sharing number 41.
for pin in ("40","41"):
    assign(esp,pin,gnd)
# Define copper track helper. USB CC straight segments are UNSAFE and not generated.
# This is deliberately only a partial routing experiment; clearance/DRC still required.
def route_pad_to_pad(source,source_number,target,target_number,network,width_mm=0.2):
    start=[p for p in source.Pads() if p.GetNumber()==source_number]
    end=[p for p in target.Pads() if p.GetNumber()==target_number]
    if len(start)!=1 or len(end)!=1:
        raise RuntimeError("Ambiguous pad number in copper route")
    track=pcb.PCB_TRACK(board)
    track.SetStart(start[0].GetPosition())
    track.SetEnd(end[0].GetPosition())
    track.SetWidth(mm(width_mm))
    track.SetLayer(pcb.F_Cu)
    track.SetNet(network)
    board.Add(track)
# USB CC traces were removed after KiCad DRC found actual shorts through adjacent connector pads.
# Re-route only after defining safe breakout geometry, clearances and vias.
# Additional short, physical EN RC interconnect; DRC must assess clearance.
route_pad_to_pad(en_pullup,"2",en_cap,"1",en)
# A short same-net power bypass between two nearby capacitors. DRC must gate
# any unexpected pad clearance or short; this is NOT a completed power plane.
route_pad_to_pad(reg_out,"1",dec,"1",v33,0.25)
# USB D+/D- and ESP32 pins are deliberately not connected until the schematic
# and connector symbol/footprint pin-number mapping have been independently reviewed.
# These are physical placements, NOT connected electrically.
pcb.SaveBoard(OUT,board)
print("Created",OUT,"footprints:",[(f.GetReference(),f.GetFPID().GetLibItemName()) for f in board.GetFootprints()])
print("WARNING: USB-C and provisional regulator pad nets assigned. Only two preliminary tracks; USB CC tracks removed due to verified shorts; no validated schematic or regulator routing. USB and LCD header order provisional and physical compatibility unverified; do not fabricate.")
